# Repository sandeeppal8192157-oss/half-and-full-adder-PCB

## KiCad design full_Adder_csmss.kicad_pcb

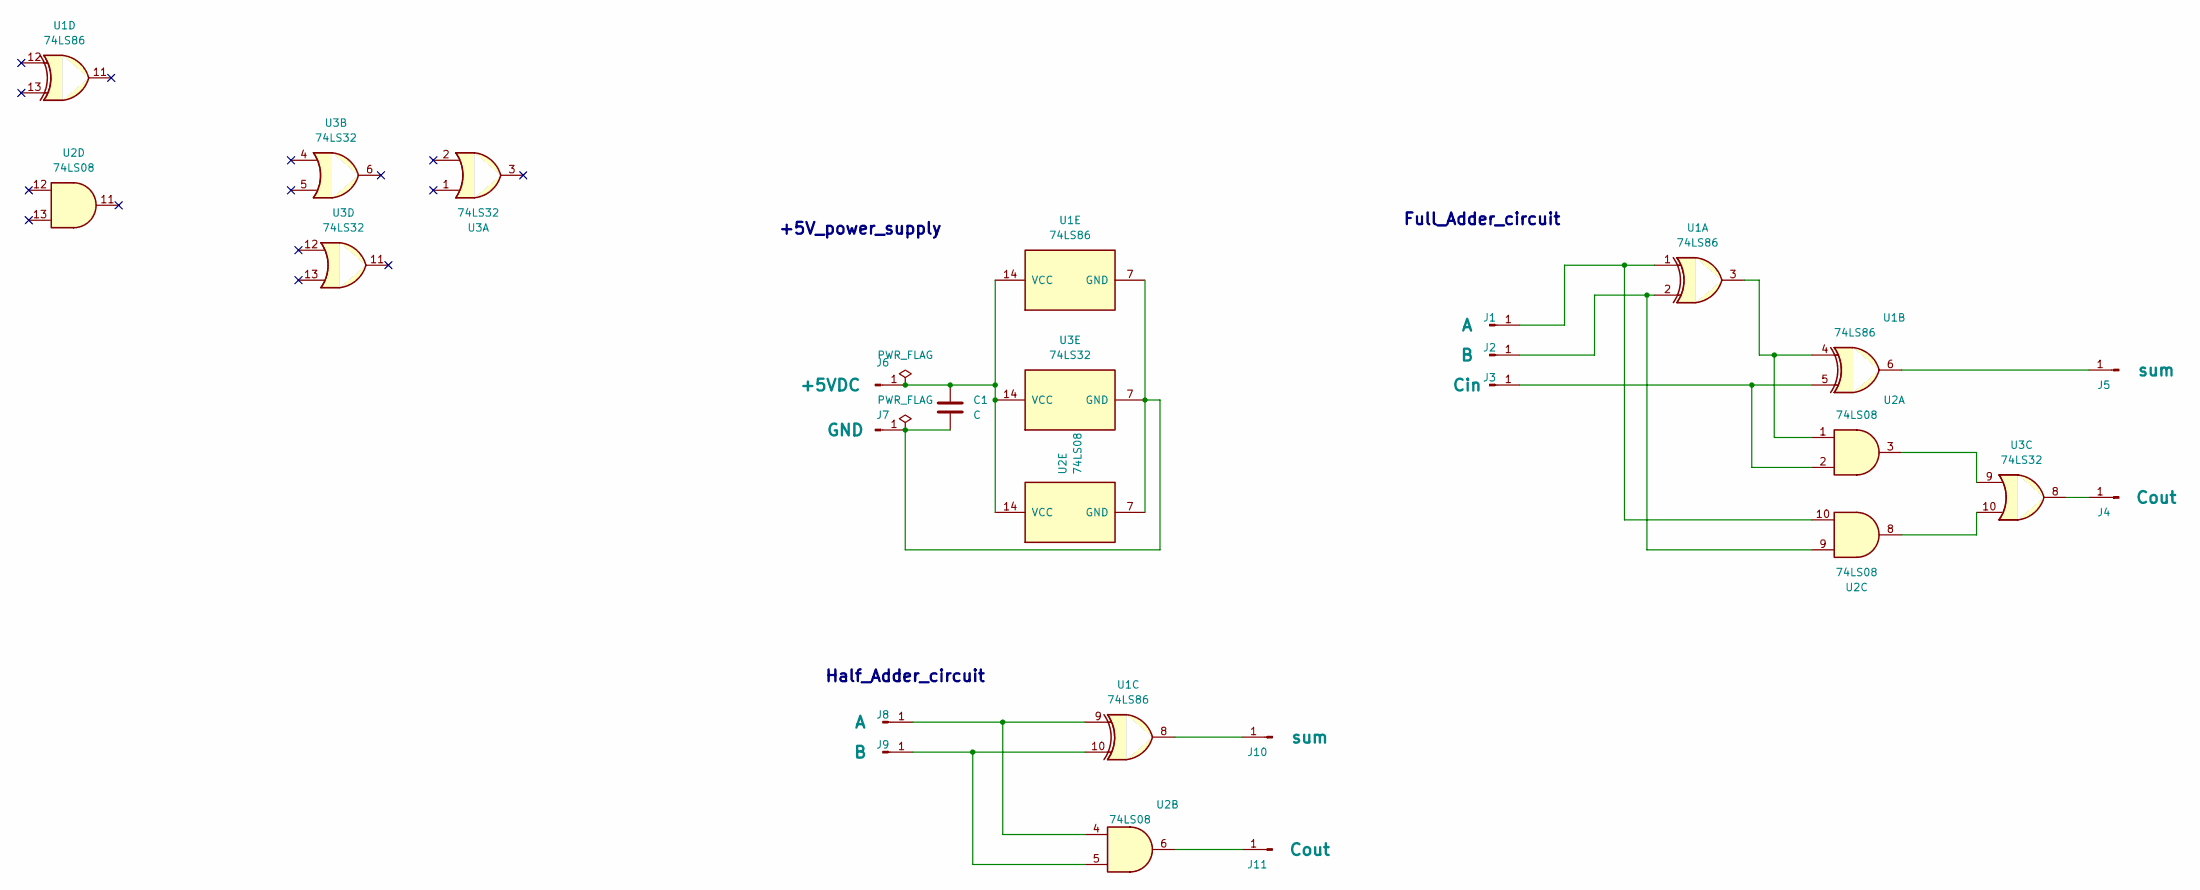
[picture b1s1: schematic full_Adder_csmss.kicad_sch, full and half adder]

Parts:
C1: C; C_Disc_D3.0mm_W2.0mm_P2.50mm
J1, J8: A; Untitled
J2, J9: B; Untitled
J3: Cin; Untitled
J4, J11: Cout; Untitled
J5, J10: sum; Untitled
J6: +5VDC; Untitled
J7: GND; Untitled
U1: 74LS86; DIP-14_W7.62mm_Socket
U2: 74LS08; DIP-14_W7.62mm_Socket
U3: 74LS32; DIP-14_W7.62mm_Socket

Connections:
unnamed: J1.1, U1.1, U2.10
unnamed: J2.1, U1.2, U2.9
unnamed: J3.1, U1.5, U2.2
unnamed: J4.1, U3.8
unnamed: J5.1, U1.6
unnamed: C1.1, J6.1, U1.14 (VCC), U2.14 (VCC), U3.14 (VCC)
unnamed: C1.2, J7.1, U1.7 (GND), U2.7 (GND), U3.7 (GND)
unnamed: J8.1, U1.9, U2.4
unnamed: J9.1, U1.10, U2.5
unnamed: J10.1, U1.8
unnamed: J11.1, U2.6
unnamed: U1.3, U1.4, U2.1
unnamed: U2.3, U3.9
unnamed: U2.8, U3.10

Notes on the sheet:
Half_Adder_circuit
+5V_power_supply
Full_Adder_circuit

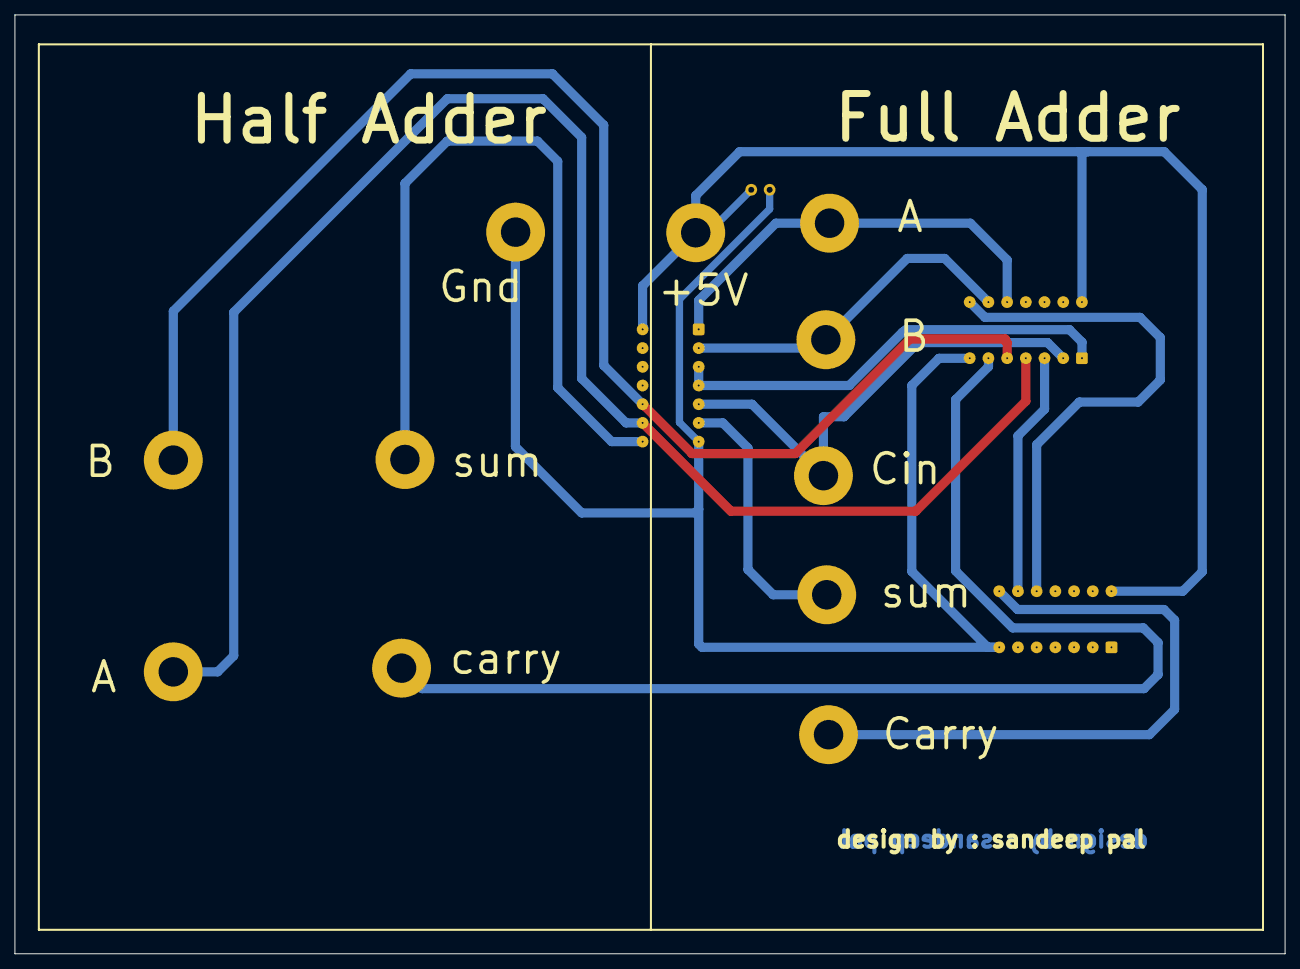
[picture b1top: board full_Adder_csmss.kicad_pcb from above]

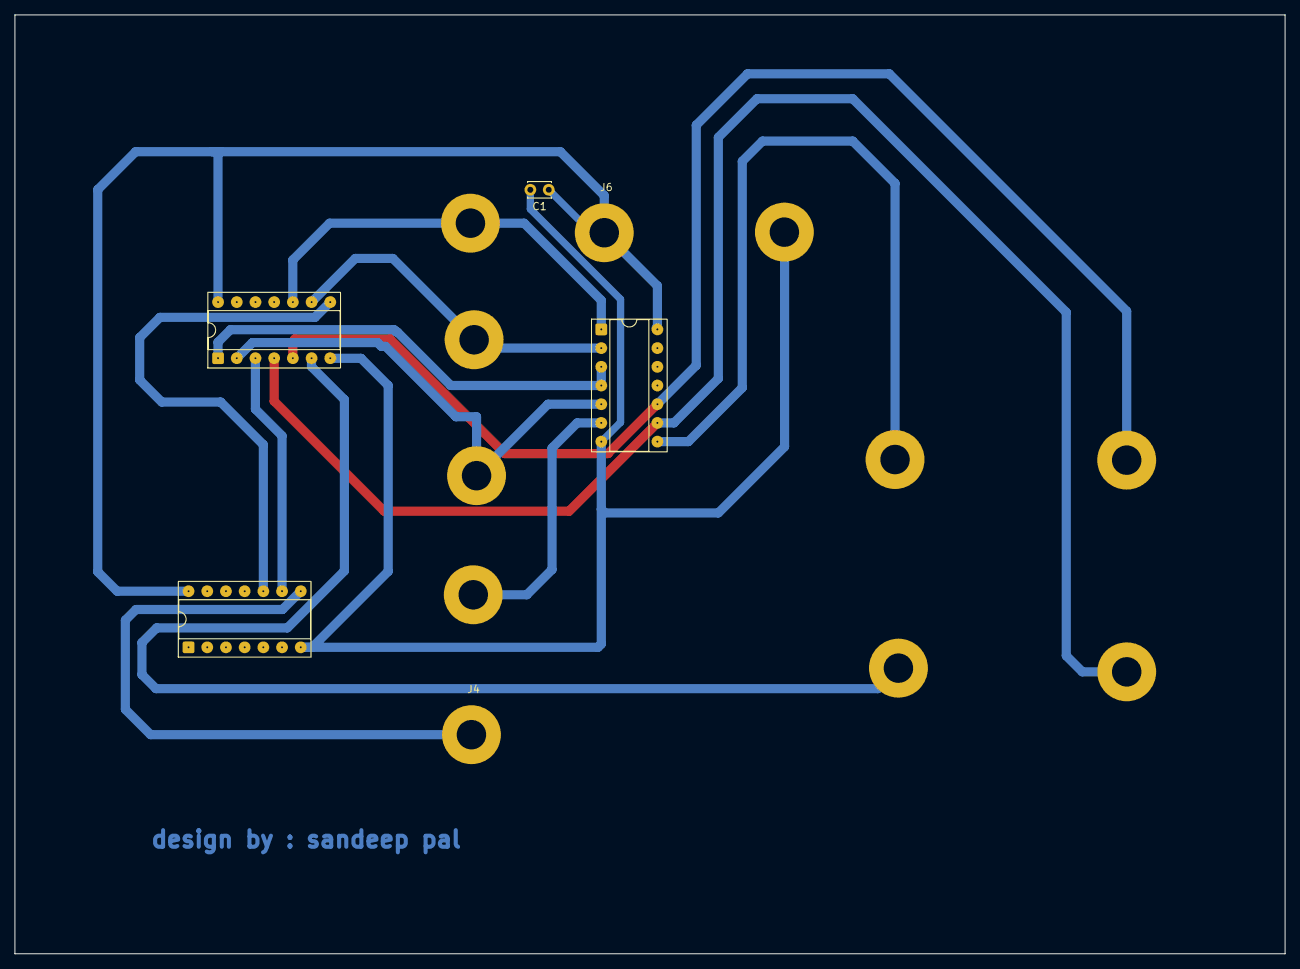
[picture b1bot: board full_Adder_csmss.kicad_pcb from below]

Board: 2 copper layers, 172.5 x 127.5 mm, 15 parts (10 on the bottom side), 14 nets.
